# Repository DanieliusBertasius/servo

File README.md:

# ❗ Servo failed right after testing, suspected potentiometer wearout

Features:
* 5.75 - 12 V input
* Stall detection at 0.8 A
* Saving last servo position in flash on power down

Notes to future self:
* Add ground test points
* Use countersunk screws if screw heads mount on bottom layer, no supports needed
* Use connectors for buttons

PSU: <br><br>

MCU: <br><br>

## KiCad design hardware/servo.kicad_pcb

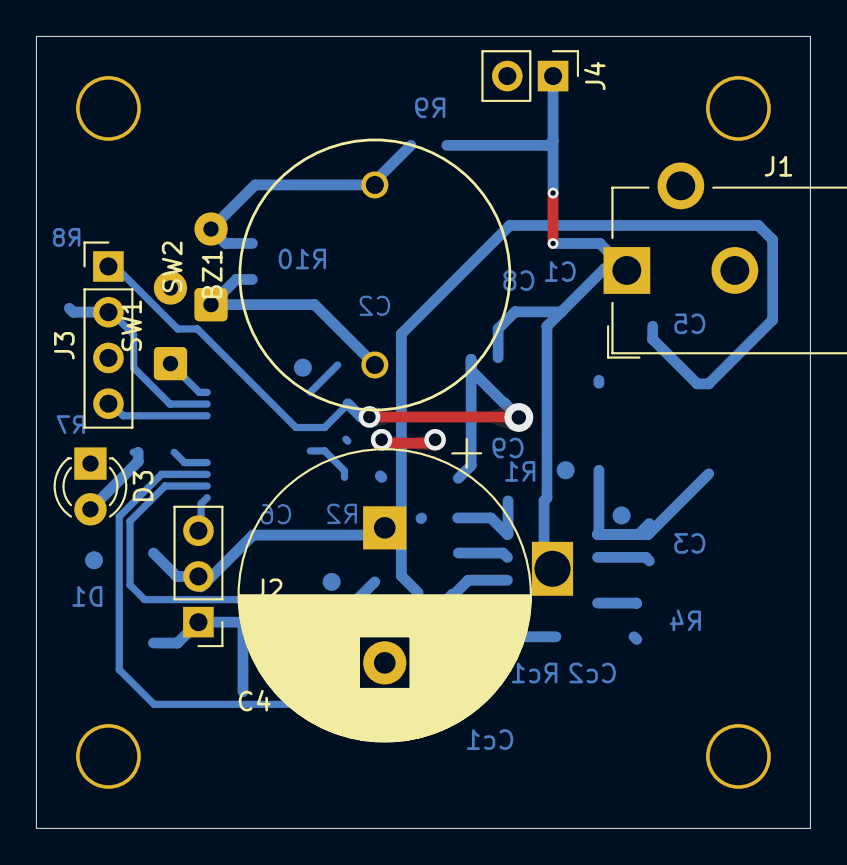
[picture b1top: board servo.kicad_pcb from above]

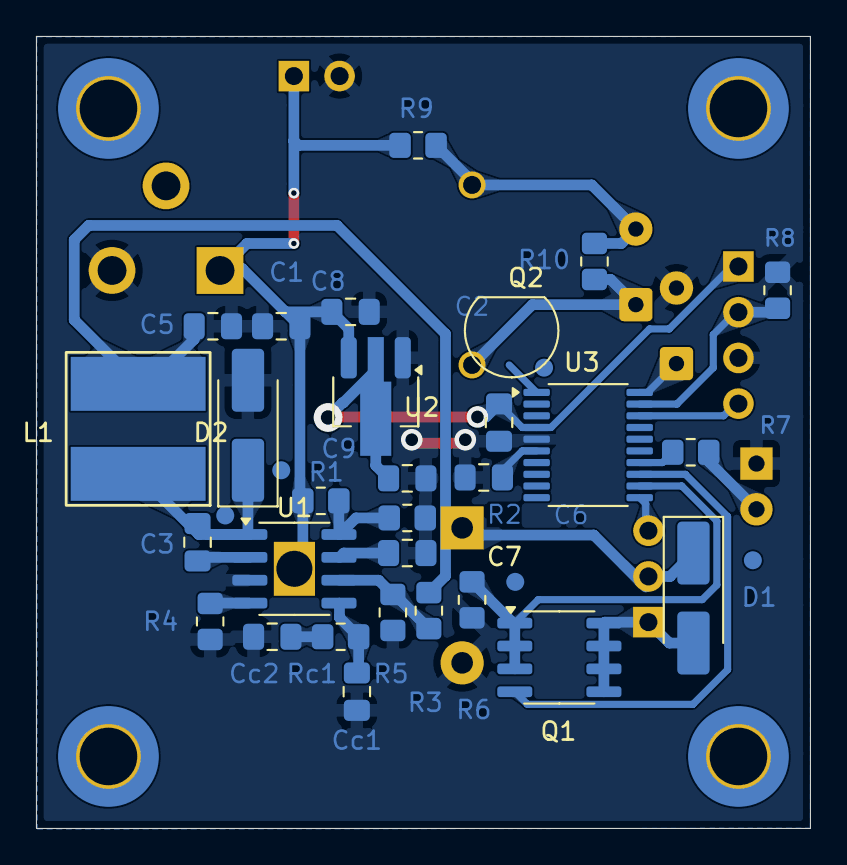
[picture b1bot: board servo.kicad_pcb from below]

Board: 2 copper layers, 43.0 x 44.0 mm, 42 parts (33 on the bottom side), 24 nets.

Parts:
BZ1: LD-BZPN-1705; LOUDITY LD-BZPN-1705
C1: 10u 16V; C_0805_2012Metric_Pad1.18x1.45mm_HandSolder
C2, C3, C6: 100n; C_0805_2012Metric_Pad1.18x1.45mm_HandSolder
C4: 4.7m; CP_Radial_D16.0mm_P7.50mm
C5: 10u; C_0805_2012Metric_Pad1.18x1.45mm_HandSolder
C7: 220n 10V; C_0805_2012Metric_Pad1.18x1.45mm_HandSolder
C8: 1u 16V; C_0805_2012Metric_Pad1.18x1.45mm_HandSolder
C9: 4.7u; C_0805_2012Metric_Pad1.18x1.45mm_HandSolder
Cc1: 150p; C_0805_2012Metric_Pad1.18x1.45mm_HandSolder
Cc2: 6.8n; C_0805_2012Metric_Pad1.18x1.45mm_HandSolder
D1, D2: SK310SMA; D_SMA_Handsoldering
D3: L-7104SURCK; LED_D3.0mm
H1, H2, H3, H4: MountingHole; MountingHole_3.2mm_M3_DIN965_Pad_TopOnly
J1: 5.5x2.1; BarrelJack_CUI_PJ-102AH_Horizontal
J2: servo; PinHeader_1x03_P2.54mm_Vertical
J3: swd; PinHeader_1x04_P2.54mm_Vertical
J4: LED; PinHeader_1x02_P2.54mm_Vertical
L1: 22u; LD2-HV
Q1: DMT64M8LSS; SOIC-8_3.9x4.9mm_P1.27mm
Q2: 2N7000; TO-92_Inline
R1, R8: 10k; R_0805_2012Metric_Pad1.20x1.40mm_HandSolder
R2, R5: 8.2k; R_0805_2012Metric_Pad1.20x1.40mm_HandSolder
R3: 43k; R_0805_2012Metric_Pad1.20x1.40mm_HandSolder
R4: 249k; R_0805_2012Metric_Pad1.20x1.40mm_HandSolder
R6: 0.22; R_0805_2012Metric_Pad1.20x1.40mm_HandSolder
R7: 150; R_0805_2012Metric_Pad1.20x1.40mm_HandSolder
R9: 1k; R_0805_2012Metric_Pad1.20x1.40mm_HandSolder
R10: 3k; R_0805_2012Metric_Pad1.20x1.40mm_HandSolder
Rc1: 1M; R_0805_2012Metric_Pad1.20x1.40mm_HandSolder
SW1: restart; SolderWire-0.25sqmm_1x02_P4.2mm_D0.65mm_OD1.7mm
SW2: buzzer; SolderWire-0.25sqmm_1x02_P4.2mm_D0.65mm_OD1.7mm
U1: AOZ1284PI; SOIC-8-1EP_3.9x4.9mm_P1.27mm_EP2.29x3mm_diy
U2: LDI1117-3.3U-DIO; SOT-89-3_Handsoldering
U3: STM32G030F6Px; TSSOP-20_4.4x6.5mm_P0.65mm

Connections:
+3V3: C2.1, C9.1, J3.1, U2.2 (VO), U3.4 (VDD)
+5V: C4.1, C5.1, D1.1 (K), J2.2, L1.2, R3.1
+12V: C1.1, C8.1, J1.1, J4.1, R1.1, R9.2, U1.9 (VIN), U2.3 (VI)
/fet: Q1.4 (G), U3.13 (PA6)
/pwm: J2.3, U3.11 (PA4)
/rst: C6.1, U3.6 (NRST)
/shunt: Q1.1 (S), Q1.2 (S), Q1.3 (S), R6.1, U3.12 (PA5)
/swclk: J3.2, R8.1, U3.19 (PA14/PA15)
/swdio: J3.4, U3.18 (PA13)
GND: C1.2, C2.2, C4.2, C5.2, C6.2, C7.2, C8.2, C9.2, Cc1.2, Cc2.2, D2.2 (A), D3.1 (K), J1.2, J3.3, J4.2, R2.2, R4.2, R5.2, R6.2, R8.2, SW1.2 (B), U1.3 (GND), U2.1 (GND), U3.5 (VSS)
unnamed: BZ1.1 (+), R10.1, SW2.1 (A)
unnamed: BZ1.2 (-), R9.1, R10.2, SW2.2 (B)
unnamed: Cc2.1, Rc1.2
unnamed: D1.2 (A), J2.1, Q1.5 (D), Q1.6 (D), Q1.7 (D), Q1.8 (D)
unnamed: C3.2, D2.1 (K), L1.1, U1.1 (LX)
unnamed: D3.2 (A), R7.2
unnamed: SW1.1 (A), U3.20 (PB3/PB4/PB5/PB6)
unnamed: C3.1, U1.2 (BST)
unnamed: Cc1.1, Rc1.1, U1.5 (COMP)
unnamed: R1.2, R2.1, U1.8 (EN)
unnamed: R3.2, R5.1, U1.6 (FB)
unnamed: R4.1, U1.4 (FSW)
unnamed: C7.1, U1.7 (SS)
unnamed: R7.1, U3.14 (PA7)
